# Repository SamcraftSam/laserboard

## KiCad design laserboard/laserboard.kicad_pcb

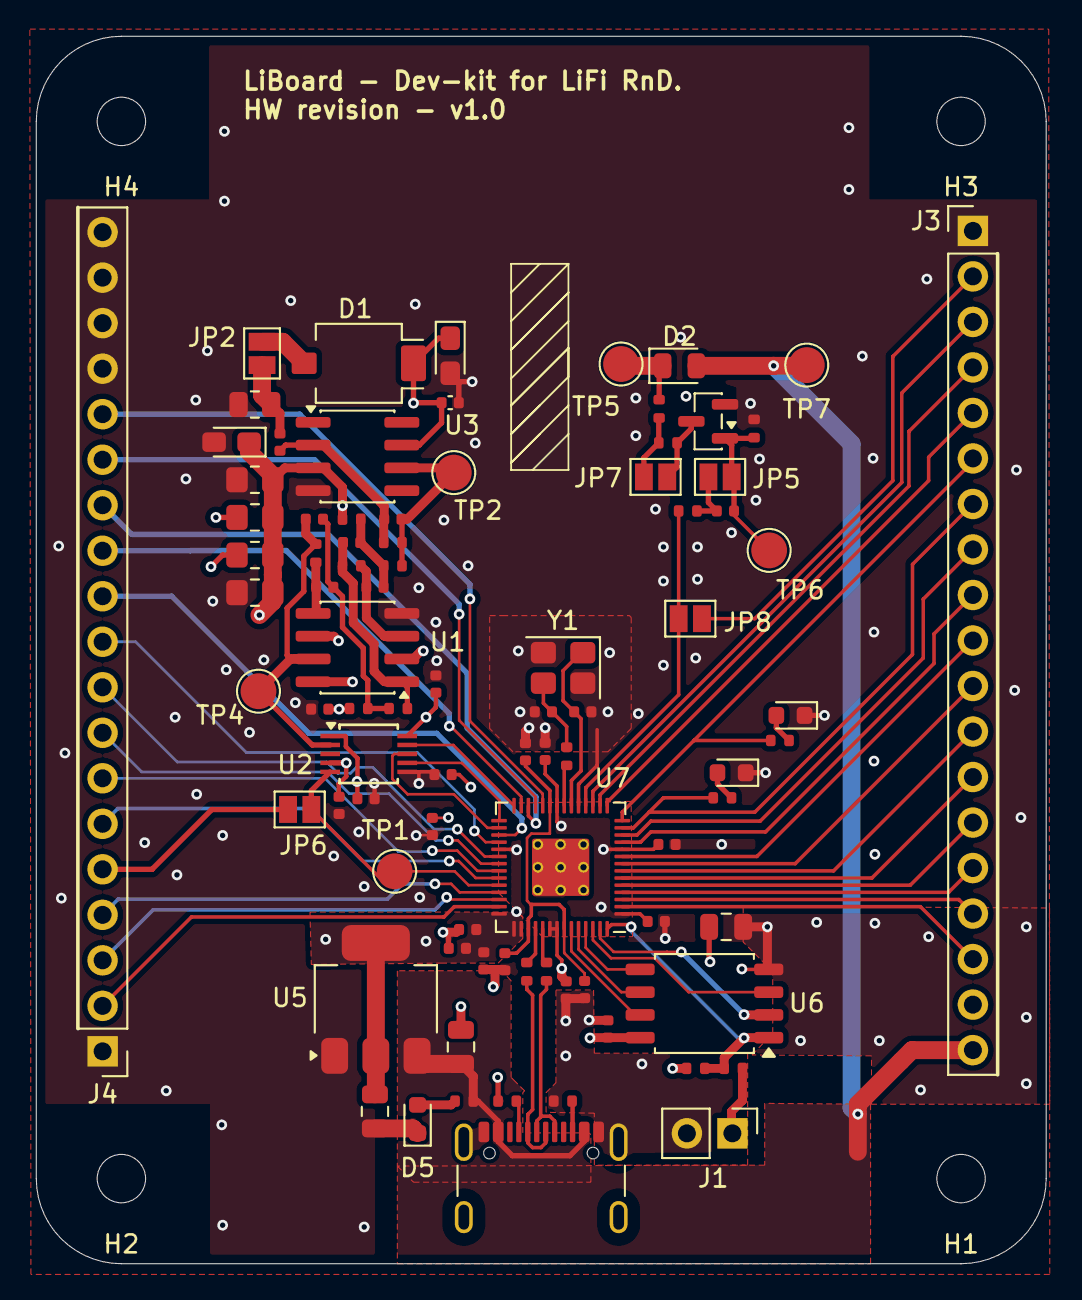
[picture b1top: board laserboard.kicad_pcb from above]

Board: 4 copper layers, 56.4 x 68.5 mm, 90 parts (0 on the bottom side), 74 nets.

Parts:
C1, C2, C4, C35: 0.1uF; C_0402_1005Metric_nosilk
C3: 2.7p; C_0402_1005Metric_nosilk
C5, C6, C15, C16: 15p; C_0402_1005Metric_nosilk
C7, C8: 33p; C_0402_1005Metric_nosilk
C14: 22n; C_0402_1005Metric_nosilk
C17, C18, C32: 10u; C_0805_2012Metric
C19, C21, C22, C24, C26, C27, C28, C29, C30, C31: 100n; C_0402_1005Metric_nosilk
C20: 10n; C_0402_1005Metric_nosilk
C23, C25: 1u; C_0402_1005Metric_nosilk
C33, C36: 4.7uF; CP_EIA-2012-12_Kemet-R_HandSolder
C34: 100p; C_0402_1005Metric_nosilk
C37: 0.1uF; C_0402_1005Metric
D1: BPW34-SMD; Osram_BPW34S-SMD
D2: LED; LED_0805_2012Metric
D3, D4, D5: LED; LED_0603_1608Metric
H1, H2, H3, H4: MountingHole; MountingHole_2.7mm_M2.5
J1: Conn_01x02; PinHeader_1x02_P2.54mm_Vertical
J2: USB_C_Receptacle_USB2.0_16P; USB_C_Receptacle_GCT_USB4105-xx-A_16P_TopMnt_Horizontal
J3, J4: Conn_01x19; PinHeader_1x19_P2.54mm_Vertical
JP2, JP6, JP8: SolderJumper_2_Open; SolderJumper-2_P1.3mm_Open_Pad1.0x1.5mm
JP5: Jumper_Filter_Bypass; SolderJumper-2_P1.3mm_Open_Pad1.0x1.5mm
JP7: Jumper_HP_MODE; SolderJumper-2_P1.3mm_Open_Pad1.0x1.5mm
N-MOS1: SOT-23
R1: 20k; R_0402_1005Metric_nosilk
R2, R3: 8.2k; R_0402_1005Metric_nosilk
R4: 33k; R_0402_1005Metric_nosilk
R5: 7.5k; R_0402_1005Metric_nosilk
R6: 6.8k; R_0402_1005Metric_nosilk
R8: 27k; R_0402_1005Metric_nosilk
R13: 40; R_0402_1005Metric_nosilk
R14: 10; R_0402_1005Metric_nosilk
R15: 75k; R_0402_1005Metric_nosilk
R16, R18, R31: 1k; R_0402_1005Metric_nosilk
R17: DNF; R_0402_1005Metric_nosilk
R19, R20: 27; R_0402_1005Metric_nosilk
R21, R22: 5.1k; R_0402_1005Metric_nosilk
R23, R24: 220k; R_0805_2012Metric_Pad1.20x1.40mm_HandSolder
R25, R26: RSHUNT_BACKUP; R_0805_2012Metric_Pad1.20x1.40mm_HandSolder
R27: 220; R_0402_1005Metric_nosilk
R28, R30: 470; R_0402_1005Metric_nosilk
R29: 1.6M; R_0805_2012Metric
TP1, TP2, TP4, TP5, TP6, TP7: TestPoint; TestPoint_Pad_D2.0mm
U1: AD8656; SOIC-8_3.9x4.9mm_P1.27mm
U2: PGA112; TSSOP-10_3x3mm_P0.5mm
U3: AD8655; SOIC-8_3.9x4.9mm_P1.27mm
U5: NCP1117-3.3_SOT223; SOT-223-3_TabPin2
U6: W25Q128JVS; SOIC-8_5.3x5.3mm_P1.27mm
U7: RP2040; RP2040-QFN-56
Y1: ABM8-272-T3; Crystal_SMD_3225-4Pin_3.2x2.5mm

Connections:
+1V1: C21.1, C22.1, C23.1, U7.23 (DVDD), U7.45 (VREG_VOUT), U7.50 (DVDD)
+3V3: C2.2, C4.1, C18.1, C19.1, C24.1, C25.1, C26.1, C27.1, C28.1, C29.1, C30.1, C31.1, C32.1, C35.1, C36.1, C37.1, D1.1 (K), J3.18, R17.1, R23.2, R25.1, U1.8 (V+), U2.1 (AV_{DD}), U2.10 (DV_{DD}), U3.7 (V+), U5.2 (VO), U6.8 (VCC), U7.1 (IOVDD), U7.10 (IOVDD), U7.22 (IOVDD), U7.33 (IOVDD), U7.42 (IOVDD), U7.43 (ADC_AVDD), U7.44 (VREG_IN), U7.48 (USB_VDD), U7.49 (IOVDD)
+5V: C17.1, D2.2 (A), J2.A4 (VBUS), J2.A9 (VBUS), J3.19, R31.2, TP7.1, U5.3 (VI)
/Didital/GPIO0: J3.17, U7.2 (GPIO0)
/Didital/GPIO1: J3.16, U7.3 (GPIO1)
/Didital/GPIO2: J3.15, U7.4 (GPIO2)
/Didital/GPIO3: J3.14, U7.5 (GPIO3)
/Didital/GPIO4: J3.13, U7.6 (GPIO4)
/Didital/GPIO5: J3.12, U7.7 (GPIO5)
/Didital/GPIO6: J3.11, U7.8 (GPIO6)
/Didital/GPIO7: J3.10, U7.9 (GPIO7)
/Didital/GPIO8: J3.9, U7.11 (GPIO8)
/Didital/GPIO9: J3.8, U7.12 (GPIO9)
/Didital/GPIO10: J3.7, R28.2, U7.13 (GPIO10)
/Didital/GPIO11: J3.6, R30.2, U7.14 (GPIO11)
/Didital/GPIO12: J3.5, U7.15 (GPIO12)
/Didital/GPIO13: J3.4, U7.16 (GPIO13)
/Didital/GPIO14: J3.3, U7.17 (GPIO14)
/Didital/GPIO15: J3.2, JP8.2 (B)
/Didital/GPIO16: J4.12, U7.27 (GPIO16)
/Didital/GPIO17: U2.9 (~CS), U7.28 (GPIO17)
/Didital/GPIO18: U2.7 (SCLK), U7.29 (GPIO18)
/Didital/GPIO19: U2.8 (DIO), U7.30 (GPIO19)
/Didital/GPIO20: J4.11, U7.31 (GPIO20)
/Didital/GPIO21: J4.10, U7.32 (GPIO21)
/Didital/GPIO22: J4.9, U7.34 (GPIO22)
/Didital/GPIO23: J4.8, U7.35 (GPIO23)
/Didital/GPIO24: J4.7, U7.36 (GPIO24)
/Didital/GPIO25: J4.6, U7.37 (GPIO25)
/Didital/GPIO26_ADC0: J4.5, JP6.2 (B)
/Didital/GPIO27_ADC1: J4.4, U7.39 (GPIO27_ADC1)
/Didital/GPIO28_ADC2: J4.3, U7.40 (GPIO28_ADC2)
/Didital/GPIO29_ADC3: J4.2, U7.41 (GPIO29_ADC3)
/Didital/QSPI_SCLK: U6.6 (CLK), U7.52 (QSPI_SCLK)
/Didital/QSPI_SD0: U6.5 (DI(IO0)), U7.53 (QSPI_SD0)
/Didital/QSPI_SD1: U6.2 (DO(IO1)), U7.55 (QSPI_SD1)
/Didital/QSPI_SD2: U6.3 (IO2), U7.54 (QSPI_SD2)
/Didital/QSPI_SD3: U6.7 (IO3), U7.51 (QSPI_SD3)
/Didital/QSPI_SS: R16.1, R17.2, U6.1 (~CS), U7.56 (QSPI_SS)
/Didital/RUN: J4.13, U7.26 (RUN)
/Didital/RX_IN: JP6.1 (A), TP1.1, U2.5 (V_{OUT}), U7.38 (GPIO26_ADC0)
/Didital/SWCLK: J4.15, U7.24 (SWCLK)
/Didital/SWD: J4.14, U7.25 (SWD)
/Didital/TX_D_IN: JP8.1 (A), R14.1, U7.18 (GPIO15)
/Didital/USB_D+: J2.A6 (D+), J2.B6 (D+), R19.1
/Didital/USB_D-: J2.A7 (D-), J2.B7 (D-), R20.1
/Didital/XIN: C15.1, U7.20 (XIN), Y1.1
/Didital/XOUT: R18.1, U7.21 (XOUT)
/Didital/~USB_BOOT: J1.1, R16.2
/RX frontend/RX_Filtered: C7.2, R8.2, TP4.1, U1.7, U2.2 (CH1)
/RX frontend/RX_Raw: C3.2, R1.2, R2.1, TP2.1, U3.6
/RX frontend/Vref_Filter: C1.1, C33.1, C34.1, R3.1, R6.1, R23.1, R24.2, R25.2, R26.1, U1.2 (-), U1.6 (-), U2.4 (V_{REF}), U3.3 (+)
GND: C1.2, C2.1, C4.2, C15.2, C16.2, C17.2, C18.2, C19.2, C21.2, C22.2, C23.2, C24.2, C25.2, C26.2, C27.2, C28.2, C29.2, C30.2, C31.2, C32.2, C33.2, C34.2, C35.2, C36.2, C37.2, D3.1 (K), D4.1 (K), D5.1 (K), J1.2, J2.A1 (GND), J2.A12 (GND), J2.S1 (SHIELD), J3.1, J4.1, J4.16, J4.17, J4.18, J4.19, N-MOS1.2 (S), R15.1, R21.2, R22.2, R24.1, R26.2, R29.1, U1.4 (V-), U2.6 (GND), U3.4 (V-), U5.1 (GND), U6.4 (GND), U7.19 (TESTEN), U7.57 (GND), Y1.2, Y1.4
unnamed: C5.1, C6.1, R2.2, R3.2
unnamed: C5.2, R4.2, R5.1, U1.1
unnamed: C7.1, C8.1, R5.2, R6.2
unnamed: C16.1, R18.2, Y1.3
unnamed: D1.2 (A), JP2.2 (B)
unnamed: D2.1 (K), R13.2, TP5.1
unnamed: D3.2 (A), R28.1
unnamed: D4.2 (A), R30.1
unnamed: D5.2 (A), R31.1
unnamed: J2.A5 (CC1), R21.1
unnamed: J2.B5 (CC2), R22.1
unnamed: C20.2, JP2.1 (A), R29.2
unnamed: C14.2, JP5.1 (A), N-MOS1.1 (G), R15.2, TP6.1
unnamed: C14.1, JP5.2 (B), R14.2
unnamed: JP7.1 (A), R13.1, R27.2
unnamed: JP7.2 (B), N-MOS1.3 (D), R27.1
unnamed: C6.2, R4.1, U1.3 (+)
unnamed: C8.2, R8.1, U1.5 (+)
unnamed: C3.1, C20.1, R1.1, U3.2 (-)
unnamed: R20.2, U7.46 (USB_DM)
unnamed: R19.2, U7.47 (USB_DP)

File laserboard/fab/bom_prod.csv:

"Designator","Comment","Quantity","Footprint"
"C1,C2,C4,C35,C37","0.1uF","5","Capacitor_SMD:C_0402"
"C3","2.7p","1","Capacitor_SMD:C_0402"
"C5,C6,C15,C16","15p","4","Capacitor_SMD:C_0402"
"C7,C8","33p","2","Capacitor_SMD:C_0402"
"C14","22n","1","Capacitor_SMD:C_0402"
"C17,C18,C32","10u","3","Capacitor_SMD:C_0805_2012Metric"
"C19,C21,C22,C24,C26,C27,C28,C29,C30,C31","100n","10","Capacitor_SMD:C_0402"
"C20","10n","1","Capacitor_SMD:C_0402"
"C23,C25","1u","2","Capacitor_SMD:C_0402"
"C33,C36","4.7uF","2","Capacitor_Tantalum_SMD:CP_EIA-2012-12_Kemet-R_HandSolder"
"C34","100p","1","Capacitor_SMD:C_0402"
"D1","BPW34-SMD","1","OptoDevice:Osram_BPW34S-SMD"
"D2","vsmy1850IT","1","LED_SMD:LED_0805_2012Metric"
"D3,D4,D5","LED","3","LED_SMD:LED_0603_1608Metric"
"H1,H2,H3,H4","MountingHole","4","MountingHole:MountingHole_2.7mm_M2.5"
"J1","Conn_01x02","1","Connector_PinHeader_2.54mm:PinHeader_1x02_P2.54mm_Vertical"
"J2","USB_C_Receptacle_USB2.0_16P","1","Connector_USB:USB_C_Receptacle_GCT_USB4105"
"J3,J4","Conn_01x19","2","Connector_PinHeader_2.54mm:PinHeader_1x19_P2.54mm_Vertical"
"N-MOS1","~","1","Package_TO_SOT_SMD:SOT-23"
"R1","20k","1","Resistor_SMD:R_0402"
"R2,R3","8.2k","2","Resistor_SMD:R_0402"
"R4","33k","1","Resistor_SMD:R_0402"
"R5","7.5k","1","Resistor_SMD:R_0402"
"R6","6.8k","1","Resistor_SMD:R_0402"
"R8","27k","1","Resistor_SMD:R_0402"
"R13","39","1","Resistor_SMD:R_0402"
"R14","10","1","Resistor_SMD:R_0402"
"R15","75k","1","Resistor_SMD:R_0402"
"R16,R18,R31","1k","3","Resistor_SMD:R_0402"
"R19,R20","27","2","Resistor_SMD:R_0402"
"R21,R22","5.1k","2","Resistor_SMD:R_0402"
"R23,R24","220k","2","Resistor_SMD:R_0805_2012Metric_Pad1.20x1.40mm_HandSolder"
"R27","220","1","Resistor_SMD:R_0402"
"R28,R30","470","2","Resistor_SMD:R_0402"
"R29","1.6M","1","Resistor_SMD:R_0805_2012Metric"
"TP1,TP2,TP4,TP5,TP6,TP7","TestPoint","6","TestPoint:TestPoint_Pad_D2.0mm"
"U1","AD8656","1","Package_SO:SOIC-8_3.9x4.9mm_P1.27mm"
"U2","PGA112","1","Package_SO:TSSOP-10_3x3mm_P0.5mm"
"U3","AD8655","1","Package_SO:SOIC-8_3.9x4.9mm_P1.27mm"
"U5","NCP1117-3.3_SOT223","1","Package_TO_SOT_SMD:SOT-223-3_TabPin2"
"U6","W25Q128JVS","1","Package_SO:SOIC-8_5.3x5.3mm_P1.27mm"
"U7","RP2040","1","RP2040_minimal:RP2040-QFN-56"
"Y1","ABM8-272-T3","1","Crystal:Crystal_SMD_3225-4Pin_3.2x2.5mm"

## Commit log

2025-11-08 Development backup
2025-11-10 Progress backup
2025-11-16 Backup
2025-11-20 Laserboard backup
2025-11-25 Pre-PCB backup
2025-11-26 AF PCB stage backup
2025-11-27 PCB_prot
2025-11-27 PCB_done
2025-11-29 Design update
2025-11-29 HW upload update
2025-12-04 Post-production commit
